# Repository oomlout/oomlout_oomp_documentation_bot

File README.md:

# None
## Description
None/

## Images

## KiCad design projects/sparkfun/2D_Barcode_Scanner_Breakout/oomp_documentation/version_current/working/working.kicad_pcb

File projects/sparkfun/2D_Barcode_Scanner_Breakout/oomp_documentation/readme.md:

# None

## Description
None/
## Schematic

## Bill of Materials
| Id | Designator | Footprint | Quantity | Designation | Supplier and ref |  |
| --- | --- | --- | --- | --- | --- | --- |
| 1 | R3,R2 | 0603 | 2 | 5.1k |  |  |
| 2 | U$1,U$7 | ##TRIG##0 | 2 |  |  |  |
| 3 | H2,H3 | STAND-OFF | 2 | STAND-OFF |  |  |
| 4 | J4 | 1X06_NO_SILK | 1 |  |  |  |
| 5 | J2 | USB-C-16P-2LAYER-PAD<br>S | 1 |  |  |  |
| 6 | S2 | TACTILE_SWITCH_SMD_5<br>.2MM | 1 | MOMENTARY-SWITCH-SPS<br>T-SMD-5.2MM-TALL |  |  |
| 7 | Q1,Q2 | SOT23-3 | 2 | 600mA/40V |  |  |
| 8 | U$8 | PWR0 | 1 |  |  |  |
| 9 | R1 | 0603 | 1 | 100 |  |  |
| 10 | U$17,U$18 | 2D_BARCODE0 | 2 |  |  |  |
| 11 | C2,C1 | 0603 | 2 | 1.0uF |  |  |
| 12 | D1 | LED-0603 | 1 | RED |  |  |
| 13 | FRAME1 | CREATIVE_COMMONS | 1 | FRAME-LETTER |  |  |
| 14 | U$26,U$27 | #TX_#0 | 2 |  |  |  |
| 15 | R7 | 0603 | 1 | 10 |  |  |
| 16 | U$32,U$33 | #GND_#0 | 2 |  |  |  |
| 17 | U$19 | SCANNER0 | 1 |  |  |  |
| 18 | U$30,U$31 | #RX_#0 | 2 |  |  |  |
| 19 | LS1 | BUZZER-CCV | 1 | BUZZER-SMD |  |  |
| 20 | U$3 | STAT0 | 1 |  |  |  |
| 21 | FD2,FD1,FD3,FD4 | FIDUCIAL-MICRO | 4 | FIDUCIALUFIDUCIAL |  |  |
| 22 | U1 | SOT23-5 | 1 | 3.3V |  |  |
| 23 | R9,R4,R11 | 0603 | 3 | 1k |  |  |
| 24 | U$28,U$29 | #3#3V_#0 | 2 |  |  |  |
| 25 | J3 | FPC_12_0.5MM | 1 |  |  |  |
| 26 | R8,R10 | 0603 | 2 | 10k |  |  |
| 27 | LOGO2 | SFE_LOGO_FLAME_.1 | 1 | SFE_LOGO_FLAME.1_INC<br>H |  |  |
| 28 | U$2,U$21 | #STAT_#0 | 2 |  |  |  |
| 29 | D2 | LED-0603 | 1 | GREEN |  |  |
| 30 | C3 | 0603 | 1 | 0.1uF |  |  |
| 31 | U$4 | #SCAN#0 | 1 |  |  |  |
| 32 | BUZZ0,PWR0,PWR_LED0 | SMT-JUMPER_2_NC_TRAC<br>E_SILK | 3 | JUMPER-SMT_2_NC_TRAC<br>E_SILK |  |  |
| 33 | U$9 | #LED#0 | 1 |  |  |  |
| 34 | U$6 | #STAT_LED#0 | 1 |  |  |  |
| 35 | LOGO1 | OSHW-LOGO-S | 1 | OSHW-LOGOS |  |  |
| 36 | U$20 | SCANNER_BREAKOUT0 | 1 |  |  |  |
| 37 | U2 | BARCODE_SCANNER_MOUN<br>T | 1 | BARCODE_SCANNER_MOUN<br>T |  |  |
| 38 | U$5 | #BUZZ#0 | 1 |  |  |  |
| 39 | LOGO3 | SFE_LOGO_NAME_.1 | 1 | SFE_LOGO_NAME.1_INCH |  |  |

## Images

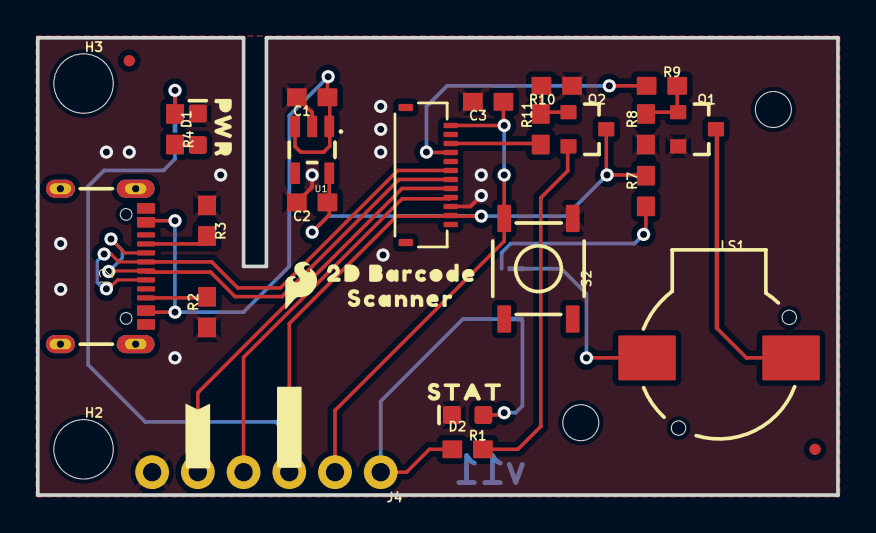
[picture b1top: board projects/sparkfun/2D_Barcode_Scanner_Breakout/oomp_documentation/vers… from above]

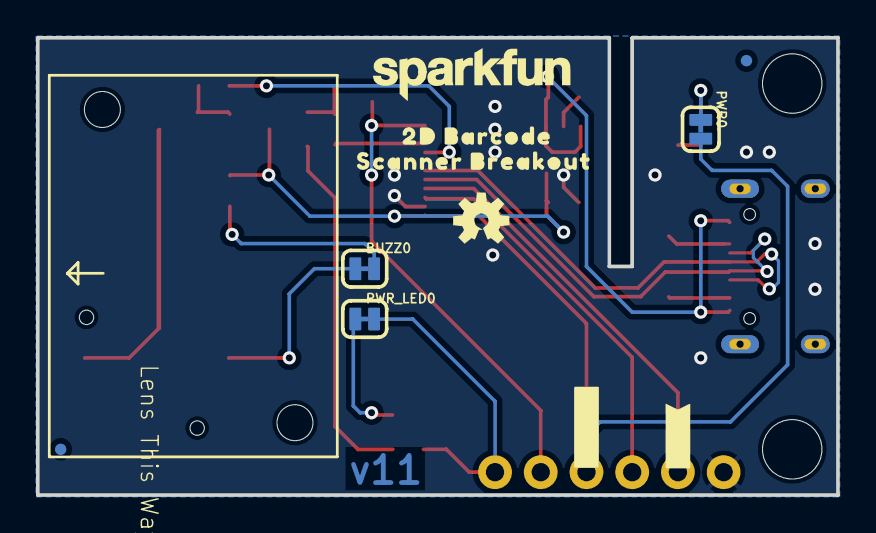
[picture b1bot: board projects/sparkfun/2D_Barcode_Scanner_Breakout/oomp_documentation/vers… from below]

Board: 2 copper layers, 44.5 x 25.4 mm, 58 parts (19 on the bottom side), 22 nets.

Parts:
BUZZ0: JUMPER-SMT_2_NC_TRACE_SILK; SMT-JUMPER_2_NC_TRACE_SILK
C1, C2: 1.0uF; 0603
C3: 0.1uF; 0603
D1: RED; LED-0603
D2: GREEN; LED-0603
FD1, FD2, FD3, FD4: FIDUCIALUFIDUCIAL; FIDUCIAL-MICRO
FRAME1: FRAME-LETTER; CREATIVE_COMMONS
H2, H3: STAND-OFF
J2: USB-C-16P-2LAYER-PADS
J3: FPC_12_0.5MM
J4: 1X06_NO_SILK
LOGO1: OSHW-LOGOS; OSHW-LOGO-S
LOGO2: SFE_LOGO_FLAME.1_INCH; SFE_LOGO_FLAME_.1
LOGO3: SFE_LOGO_NAME.1_INCH; SFE_LOGO_NAME_.1
LS1: BUZZER-SMD; BUZZER-CCV
PWR0: JUMPER-SMT_2_NC_TRACE_SILK; SMT-JUMPER_2_NC_TRACE_SILK
PWR_LED0: JUMPER-SMT_2_NC_TRACE_SILK; SMT-JUMPER_2_NC_TRACE_SILK
Q1, Q2: 600mA/40V; SOT23-3
R1: 100; 0603
R2, R3: 5.1k; 0603
R4, R9, R11: 1k; 0603
R7: 10; 0603
R8, R10: 10k; 0603
S2: MOMENTARY-SWITCH-SPST-SMD-5.2MM-TALL; TACTILE_SWITCH_SMD_5.2MM
U1: 3.3V; SOT23-5
U2: BARCODE_SCANNER_MOUNT
U$1, U$7: ##TRIG##0
U$2, U$21: #STAT_#0
U$3: STAT0
U$4: #SCAN#0
U$5: #BUZZ#0
U$6: #STAT_LED#0
U$8: PWR0
U$9: #LED#0
U$17, U$18: 2D_BARCODE0
U$19: SCANNER0
U$20: SCANNER_BREAKOUT0
U$26, U$27: #TX_#0
U$28, U$29: #3#3V_#0
U$30, U$31: #RX_#0
U$32, U$33: #GND_#0

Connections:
3.3V: C2.1, J3.11, J4.3, PWR0.2, Q2.3, R7.2, U1.5
5V: C1.1, J2.VBUS1, J2.VBUS2, U1.1, U1.3
BUZZER: J3.4, R9.1
CC3: J2.A5, R3.2
CC4: J2.B5, R2.2
GND: C1.2, C2.2, C3.2, D1.C, D2.C, J2.GND, J2.GND2, J3.10, J4.6, Q1.2, R2.1, R3.1, R8.1, R10.1, S2.1, U1.2
unnamed: BUZZ0.2, R7.1
unnamed: LS1.-, Q1.3
unnamed: BUZZ0.1, LS1.+
unnamed: Q2.2, R1.2
unnamed: Q1.1, R8.2, R9.2
unnamed: PWR0.1, R4.1
unnamed: Q2.1, R10.2, R11.2
unnamed: D2.A, PWR_LED0.1
unnamed: D1.A, R4.2
RXI: J3.9, J4.4
STATUS_LED: J3.3, R11.1
STATUS_OUT: J4.1, PWR_LED0.2, R1.1
TXO: J3.8, J4.5
USB_N: J2.A7, J2.B7, J3.7
USB_P: J2.A6, J2.B6, J3.6
~SCAN_TRIGGER: C3.1, J3.1, J4.2, S2.3

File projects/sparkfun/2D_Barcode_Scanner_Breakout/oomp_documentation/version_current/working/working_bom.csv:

"Id";"Designator";"Footprint";"Quantity";"Designation";"Supplier and ref";
1;"R3,R2";"0603";2;"5.1k";;;
2;"U$1,U$7";"##TRIG##0";2;"";;;
3;"H2,H3";"STAND-OFF";2;"STAND-OFF";;;
4;"J4";"1X06_NO_SILK";1;"";;;
5;"J2";"USB-C-16P-2LAYER-PADS";1;"";;;
6;"S2";"TACTILE_SWITCH_SMD_5.2MM";1;"MOMENTARY-SWITCH-SPST-SMD-5.2MM-TALL";;;
7;"Q1,Q2";"SOT23-3";2;"600mA/40V";;;
8;"U$8";"PWR0";1;"";;;
9;"R1";"0603";1;"100";;;
10;"U$17,U$18";"2D_BARCODE0";2;"";;;
11;"C2,C1";"0603";2;"1.0uF";;;
12;"D1";"LED-0603";1;"RED";;;
13;"FRAME1";"CREATIVE_COMMONS";1;"FRAME-LETTER";;;
14;"U$26,U$27";"#TX_#0";2;"";;;
15;"R7";"0603";1;"10";;;
16;"U$32,U$33";"#GND_#0";2;"";;;
17;"U$19";"SCANNER0";1;"";;;
18;"U$30,U$31";"#RX_#0";2;"";;;
19;"LS1";"BUZZER-CCV";1;"BUZZER-SMD";;;
20;"U$3";"STAT0";1;"";;;
21;"FD2,FD1,FD3,FD4";"FIDUCIAL-MICRO";4;"FIDUCIALUFIDUCIAL";;;
22;"U1";"SOT23-5";1;"3.3V";;;
23;"R9,R4,R11";"0603";3;"1k";;;
24;"U$28,U$29";"#3#3V_#0";2;"";;;
25;"J3";"FPC_12_0.5MM";1;"";;;
26;"R8,R10";"0603";2;"10k";;;
27;"LOGO2";"SFE_LOGO_FLAME_.1";1;"SFE_LOGO_FLAME.1_INCH";;;
28;"U$2,U$21";"#STAT_#0";2;"";;;
29;"D2";"LED-0603";1;"GREEN";;;
30;"C3";"0603";1;"0.1uF";;;
31;"U$4";"#SCAN#0";1;"";;;
32;"BUZZ0,PWR0,PWR_LED0";"SMT-JUMPER_2_NC_TRACE_SILK";3;"JUMPER-SMT_2_NC_TRACE_SILK";;;
33;"U$9";"#LED#0";1;"";;;
34;"U$6";"#STAT_LED#0";1;"";;;
35;"LOGO1";"OSHW-LOGO-S";1;"OSHW-LOGOS";;;
36;"U$20";"SCANNER_BREAKOUT0";1;"";;;
37;"U2";"BARCODE_SCANNER_MOUNT";1;"BARCODE_SCANNER_MOUNT";;;
38;"U$5";"#BUZZ#0";1;"";;;
39;"LOGO3";"SFE_LOGO_NAME_.1";1;"SFE_LOGO_NAME.1_INCH";;;

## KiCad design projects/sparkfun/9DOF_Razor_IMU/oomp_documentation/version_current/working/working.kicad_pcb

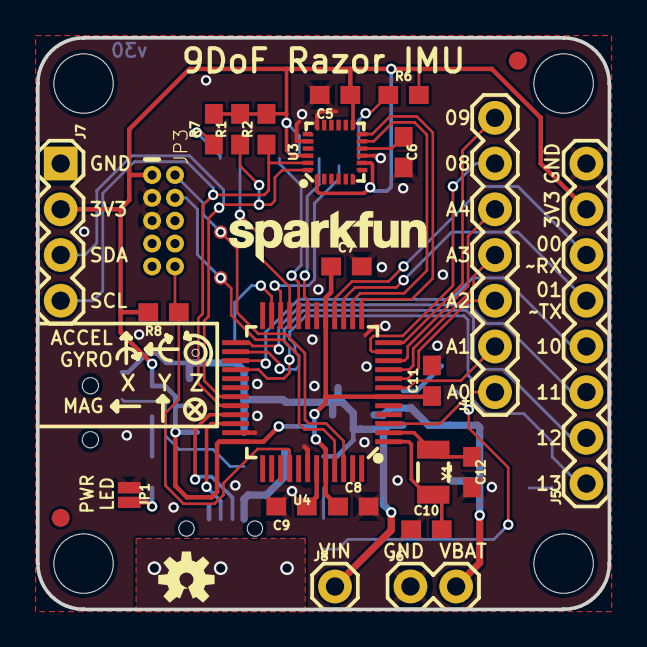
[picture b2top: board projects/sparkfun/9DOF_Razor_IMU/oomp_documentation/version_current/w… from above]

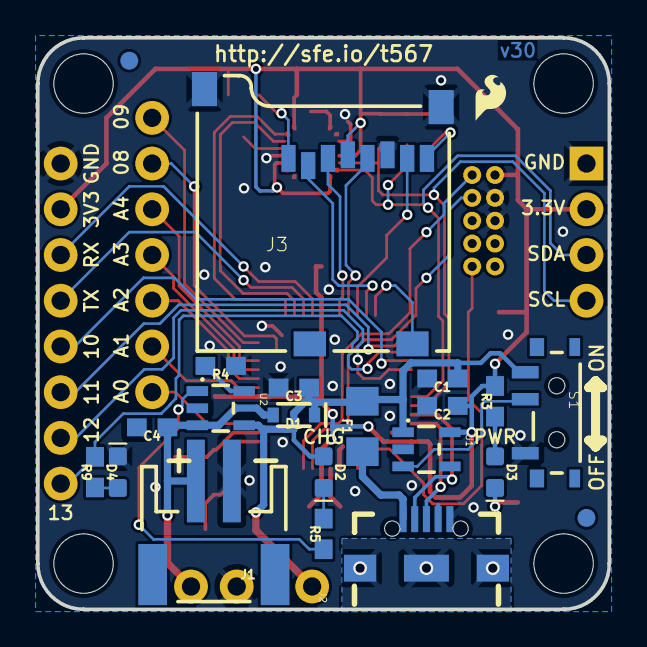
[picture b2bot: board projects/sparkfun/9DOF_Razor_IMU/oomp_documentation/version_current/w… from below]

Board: 2 copper layers, 31.8 x 31.8 mm, 56 parts (22 on the bottom side), 46 nets.

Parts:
C1: 1.0uF; 0603
C2: 2.2uF; 0603
C3, C4: 4.7uF; 0603
C5, C6, C7, C8, C9, C11: 0.1uF; 0603
C10, C12: 15pF; 0603
D1: 1A/23V/620mV; SOD-323
D2: Yellow; LED-0603
D3: RED; LED-0603
D4: BLUE; LED-0603
F1: 6V/0.5A; 1206
FD1, FD2, FD3, FD4: FIDUCIAL1X2; FIDUCIAL-1X2
FRAME1: FRAME-LETTER; CREATIVE_COMMONS
H1, H2, H3, H4: STAND-OFF
J1: LiPo; JST-2-SMD
J2: USB-B-MICRO-SMD_V03
J3: USD_CONNECTOR; MICRO-SD-SOCKET-PP
J4: 1X07
J5: 1X08
J6: 1X02
J7: 1X04
J8: 1X01
JP1: LED; SMT-JUMPER_2_NC_PASTE_NO-SILK
JP3: CORTEX_DEBUGPTH; 2X5-PTH-1.27MM
LOGO1: SFE_LOGO_FLAME.1_INCH; SFE_LOGO_FLAME_.1
LOGO2: OSHW-LOGOS; OSHW-LOGO-S
LOGO3: SFE_LOGO_NAME.1_INCH; SFE_LOGO_NAME_.1
R1, R2: 4.7k; 0603
R3, R5, R9: 1k; 0603
R4: 2.2k; 0603
R6, R7: 100k; 0603
R8: 10k; 0603
S1: SWITCH-SPST-SMD-A
TP1, TP2: TEST-POINT3; PAD.03X.03
U1: 3.3V; SOT23-5
U2: MCP73831; SOT23-5
U3: MPU-9250; QFN24-3X3
U4: ATSAMD21G-A; TQFP-48
Y1: 32.768kHz; CRYSTAL-SMD-3.2X1.5MM

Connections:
3.3V: C2.1, C5.1, C7.1, C8.1, C11.1, J3.VCC, J5.7, J7.2, JP3.1, R1.2, R2.2, R3.2, R6.2, R7.2, R8.2, U1.5, U3.1, U3.8, U3.13, U3.22, U4.6, U4.17, U4.36, U4.44
A0: J4.1, U4.3
A1: J4.2, U4.7
A2: J4.3, U4.8
A3: J4.4, U4.9
A4: J4.5, U4.10
CHG_LED: R5.1, U2.1
D0/RXI: J5.6, U4.16
D1/TXO: J5.5, U4.15
D2/SD_CD: J3.CD1, U4.23
D3/FSYNC: U3.11, U4.14
D4/INT: U3.12, U4.13
D8: J4.6, U4.11
D9: J4.7, U4.12
D10: J5.4, U4.27
D11: J5.3, U4.25
D12: J5.2, U4.28
D13: J5.1, R9.2, U4.26
D+: J2.D+, U4.34
D-: J2.D-, U4.33
GND: C1.2, C2.2, C3.2, C4.2, C5.2, C6.2, C7.2, C8.2, C9.2, C10.1, C11.2, C12.2, D4.C, J1.1, J2.GND, J3.GND, J3.GND1, J3.GND3, J5.8, J6.1, J7.1, JP1.1, JP3.3, JP3.5, R4.1, S1.3, U1.2, U2.2, U3.9, U3.18, U3.20, U4.5, U4.18, U4.35, U4.42
unnamed: F1.1, J2.VBUS
unnamed: C10.2, U4.1, Y1.P$2
unnamed: D4.A, R9.1
unnamed: C12.1, U4.2, Y1.P$1
unnamed: D3.A, R3.1
unnamed: R4.2, U2.5
unnamed: J3.RSV1, R6.1
unnamed: J3.RSV2, R7.1
unnamed: D2.C, R5.2
unnamed: D3.C, JP1.2
REGOUT: C6.1, U3.10
SCL: J7.4, R2.1, U3.23, U4.32
SDA: J7.3, R1.1, U3.24, U4.31
SD_MISO: J3.DO, U4.21
SD_MOSI: J3.DI, U4.19
SD_SCK: J3.SCLK, U4.20
SD_~CS: J3.CS, U4.22
SHIELD: J2.SHIELD1, J2.SHIELD2, J2.SHIELD3
SWCLK: JP3.4, TP1.P$1, U4.45
SWDIO: JP3.2, TP2.P$1, U4.46
VDDCORE: C9.1, U4.43
VIN: C1.1, C3.1, D1.C, D2.A, F1.2, J8.1, S1.1, U1.1, U2.4
VREG_EN: S1.2, U1.3
V_BATT: C4.1, D1.A, J1.2, J6.2, U2.3
~RESET: JP3.10, R8.1, U4.40

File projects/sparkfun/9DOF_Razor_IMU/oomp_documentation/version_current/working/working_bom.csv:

"Id";"Designator";"Footprint";"Quantity";"Designation";"Supplier and ref";
1;"H1,H2,H3,H4";"STAND-OFF";4;"STAND-OFF";;;
2;"C11,C5,C7,C9,C8,C6";"0603";6;"0.1uF";;;
3;"U4";"TQFP-48";1;"ATSAMD21G-A";;;
4;"C12,C10";"0603";2;"15pF";;;
5;"FD2,FD4,FD3,FD1";"FIDUCIAL-1X2";4;"FIDUCIAL1X2";;;
6;"Y1";"CRYSTAL-SMD-3.2X1.5MM";1;"32.768kHz";;;
7;"R6,R7";"0603";2;"100k";;;
8;"R1,R2";"0603";2;"4.7k";;;
9;"JP1";"SMT-JUMPER_2_NC_PASTE_NO-SILK";1;"LED";;;
10;"LOGO2";"OSHW-LOGO-S";1;"OSHW-LOGOS";;;
11;"J6";"1X02";1;"";;;
12;"LOGO3";"SFE_LOGO_NAME_.1";1;"SFE_LOGO_NAME.1_INCH";;;
13;"TP2,TP1";"PAD.03X.03";2;"TEST-POINT3";;;
14;"J4";"1X07";1;"";;;
15;"FRAME1";"CREATIVE_COMMONS";1;"FRAME-LETTER";;;
16;"R8";"0603";1;"10k";;;
17;"U3";"QFN24-3X3";1;"MPU-9250";;;
18;"JP3";"2X5-PTH-1.27MM";1;"CORTEX_DEBUGPTH";;;
19;"J8";"1X01";1;"";;;
20;"J7";"1X04";1;"";;;
21;"J5";"1X08";1;"";;;
22;"D3";"LED-0603";1;"RED";;;
23;"S1";"SWITCH-SPST-SMD-A";1;"SWITCH-SPST-SMD-A";;;
24;"D1";"SOD-323";1;"1A/23V/620mV";;;
25;"C2";"0603";1;"2.2uF";;;
26;"C3,C4";"0603";2;"4.7uF";;;
27;"R3,R5,R9";"0603";3;"1k";;;
28;"J3";"MICRO-SD-SOCKET-PP";1;"USD_CONNECTOR";;;
29;"F1";"1206";1;"6V/0.5A";;;
30;"C1";"0603";1;"1.0uF";;;
31;"LOGO1";"SFE_LOGO_FLAME_.1";1;"SFE_LOGO_FLAME.1_INCH";;;
32;"U1";"SOT23-5";1;"3.3V";;;
33;"J2";"USB-B-MICRO-SMD_V03";1;"";;;
34;"J1";"JST-2-SMD";1;"LiPo";;;
35;"R4";"0603";1;"2.2k";;;
36;"U2";"SOT23-5";1;"MCP73831";;;
37;"D2";"LED-0603";1;"Yellow";;;
38;"D4";"LED-0603";1;"BLUE";;;

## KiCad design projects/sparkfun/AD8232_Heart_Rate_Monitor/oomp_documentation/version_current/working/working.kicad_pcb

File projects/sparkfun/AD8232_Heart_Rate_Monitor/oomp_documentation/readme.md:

# None

## Description
None/
## Schematic

## Bill of Materials
| Id | Designator | Footprint | Quantity | Designation | Supplier and ref |  |
| --- | --- | --- | --- | --- | --- | --- |
| 1 | JP3 | 1X06 | 1 |  |  |  |
| 2 | C1 | 0603-CAP | 1 | 1.5nF |  |  |
| 3 | STANDOFF1,STANDOFF4,<br>STANDOFF3,STANDOFF2 | STAND-OFF | 4 | STAND-OFF |  |  |
| 4 | LOGO2 | SFE_LOGO_NAME_FLAME_<br>.1 | 1 | SFE_LOGO_NAME_FLAME.<br>1_INCH |  |  |
| 5 | U1 | LFCSP_20 | 1 | AD8232 |  |  |
| 6 | FRAME1 | CREATIVE_COMMONS | 1 | FRAME-LETTER |  |  |
| 7 | C7 | 0603-CAP | 1 | 0.1uf |  |  |
| 8 | R2,R13,R1,R14,R11,R1<br>0 | 0603-RES | 6 | 10M |  |  |
| 9 | R6,R7,R9 | 0603-RES | 3 | 1M |  |  |
| 10 | FID1,FID2 | FIDUCIAL-1X2 | 2 | FIDUCIAL1X2 |  |  |
| 11 | R3,R4 | 0603-RES | 2 | 180k |  |  |
| 12 | SJ4 | SJ_2S-TRACE | 1 | LED DISABLE |  |  |
| 13 | R15 | 0603-RES | 1 | 10K |  |  |
| 14 | R5 | 0603-RES | 1 | 360k |  |  |
| 15 | R18,R20 | 0603 | 2 | DNP |  |  |
| 16 | R8 | 0603-RES | 1 | 100k |  |  |
| 17 | C4,C6 | 0805 | 2 | 0.33uF |  |  |
| 18 | D1 | LED-0603 | 1 | RED |  |  |
| 19 | R16 | 0603-RES | 1 | 1k |  |  |
| 20 | C3 | 0603-CAP | 1 | 10nF |  |  |
| 21 | LOGO1 | OSHW-LOGO-S | 1 | OSHW-LOGOS |  |  |
| 22 | C5 | 0603-CAP | 1 | 0.1uF |  |  |
| 23 | JP2 | AUDIO-JACK-3.5MM-SMD | 1 |  |  |  |
| 24 | R12 | 0603-RES | 1 | 1.4M |  |  |
| 25 | R17,R19 | 0603 | 2 | 0 |  |  |
| 26 | C2 | 0603-CAP | 1 | 1nF |  |  |
| 27 | JP1 | 1X03 | 1 |  |  |  |

## Images

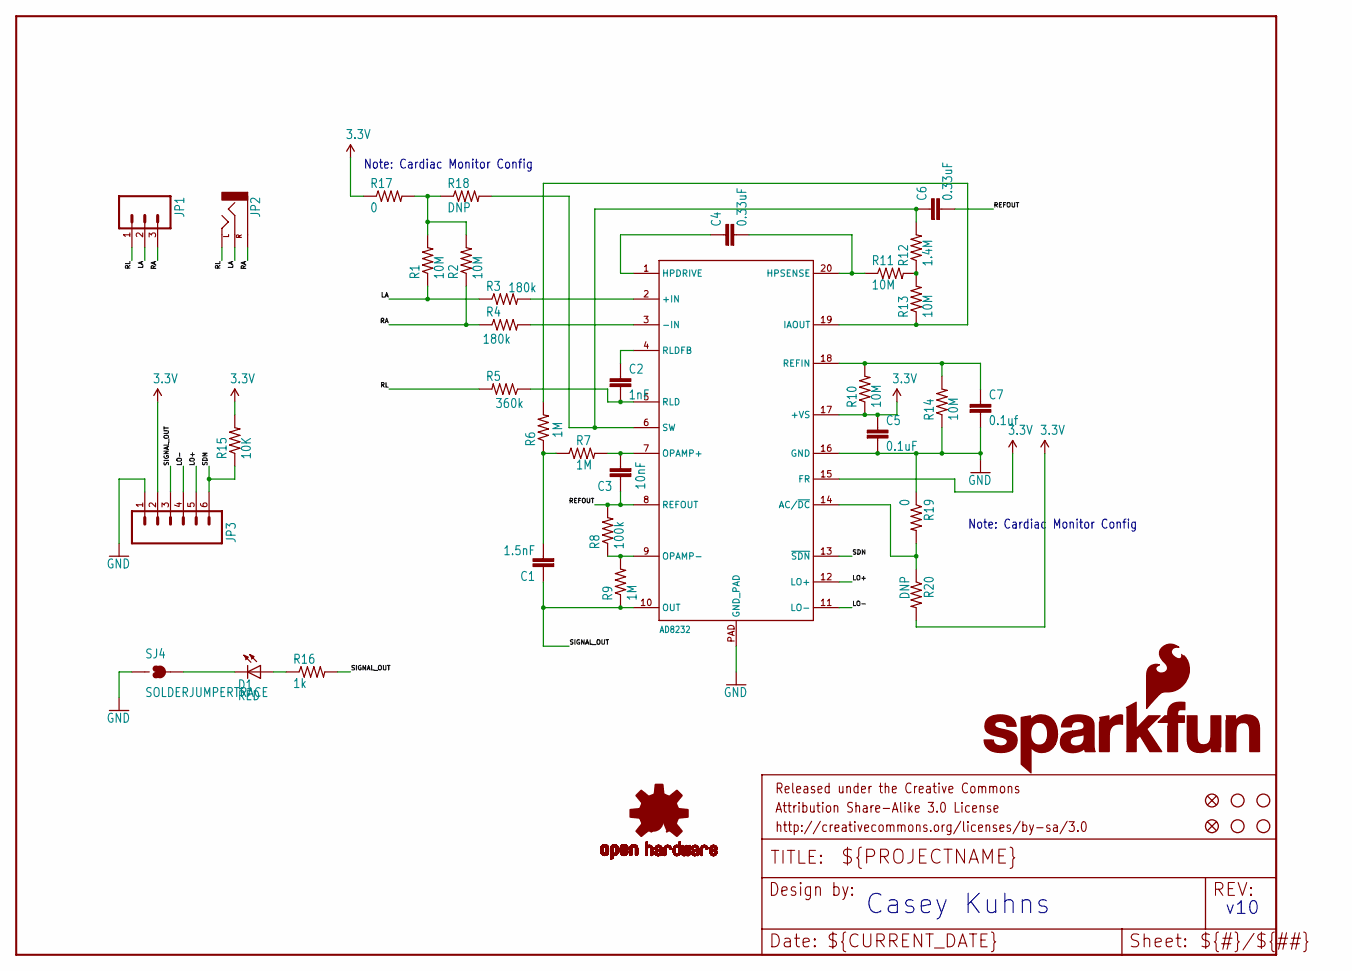
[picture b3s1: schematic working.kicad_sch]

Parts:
C1: 1.5nF; 0603-CAP
C2: 1nF; 0603-CAP
C3: 10nF; 0603-CAP
C4, C6: 0.33uF; 0805
C5: 0.1uF; 0603-CAP
C7: 0.1uf; 0603-CAP
D1: RED; LED-0603
FID1, FID2: FIDUCIAL1X2; FIDUCIAL-1X2
FRAME1: FRAME-LETTER; CREATIVE_COMMONS
JP1: M03PTH; 1X03
JP2: AUDIO-JACKSMD2; AUDIO-JACK-3.5MM-SMD
JP3: M06SIP; 1X06
LOGO1: OSHW-LOGOS; OSHW-LOGO-S
LOGO2: SFE_LOGO_NAME_FLAME.1_INCH; SFE_LOGO_NAME_FLAME_.1
R1, R2, R10, R11, R13, R14: 10M; 0603-RES
R3, R4: 180k; 0603-RES
R5: 360k; 0603-RES
R6, R7, R9: 1M; 0603-RES
R8: 100k; 0603-RES
R12: 1.4M; 0603-RES
R15: 10K; 0603-RES
R16: 1k; 0603-RES
R17, R19: 0; 0603
R18, R20: DNP; 0603
SJ4: SOLDERJUMPERTRACE; SJ_2S-TRACE
STANDOFF1, STANDOFF2, STANDOFF3, STANDOFF4: STAND-OFF
U1: AD8232; LFCSP_20

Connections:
3.3V: C5.1, JP3.2, R10.1, R15.2, R17.1, R20.2, U1.15 (FR), U1.17 (+VS)
GND: C5.2, C7.2, JP3.1, R14.1, R19.1, SJ4.1, U1.16 (GND), U1.PAD (GND_PAD)
LA: JP1.2, JP2.RING (RIGHT), R1.1, R3.1
LO+: JP3.5, U1.12 (LO+)
LO-: JP3.4, U1.11 (LO-)
unnamed: R3.2, U1.2 (+IN)
unnamed: R4.2, U1.3 (-IN)
unnamed: C3.2, R7.2, U1.7 (OPAMP+)
unnamed: C4.2, R11.1, U1.20 (HPSENSE)
unnamed: C7.1, R10.2, R14.2, U1.18 (REFIN)
unnamed: D1.A, R16.1
unnamed: R8.1, R9.2, U1.9 (OPAMP-)
unnamed: R6.2, R13.1, U1.19 (IAOUT)
unnamed: C1.2, R6.1, R7.1
unnamed: D1.C, SJ4.2
unnamed: R19.2, R20.1, U1.14 (AC/~DC)
unnamed: C4.1, U1.1 (HPDRIVE)
unnamed: R11.2, R12.1, R13.2
unnamed: C6.1, R12.2, R18.2, U1.6 (SW)
unnamed: C2.1, U1.4 (RLDFB)
unnamed: C2.2, R5.1, U1.5 (RLD)
unnamed: R1.2, R2.2, R17.2, R18.1
RA: JP1.3, JP2.SLEEVE, R2.1, R4.1
REFOUT: C3.1, C6.2, R8.2, U1.8 (REFOUT)
RL: JP1.1, JP2.TIP (LEFT), R5.2
SDN: JP3.6, R15.1, U1.13 (~SDN)
SIGNAL_OUT: C1.1, JP3.3, R9.1, R16.2, U1.10 (OUT)

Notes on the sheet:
v10
Casey Kuhns
Note: Cardiac Monitor Config

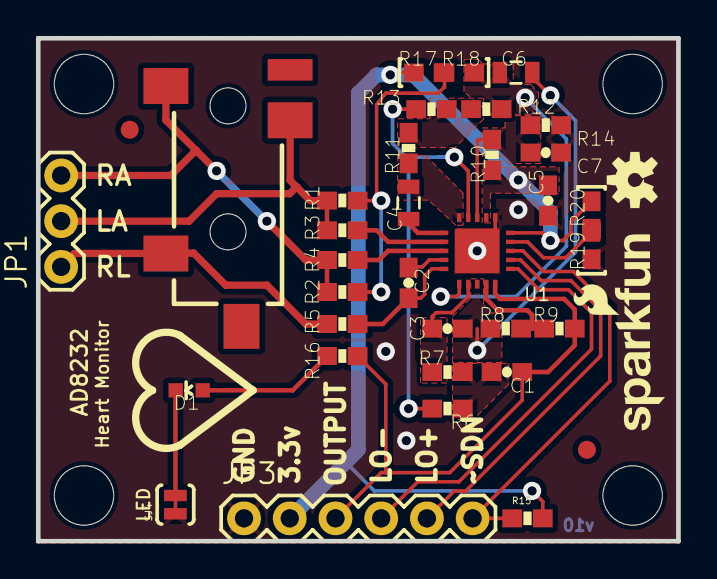
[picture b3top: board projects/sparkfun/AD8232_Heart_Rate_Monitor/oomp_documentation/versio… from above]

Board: 2 copper layers, 35.6 x 27.9 mm, 42 parts (0 on the bottom side), 27 nets.

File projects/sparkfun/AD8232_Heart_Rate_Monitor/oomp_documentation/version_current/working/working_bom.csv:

"Id";"Designator";"Footprint";"Quantity";"Designation";"Supplier and ref";
1;"JP3";"1X06";1;"";;;
2;"C1";"0603-CAP";1;"1.5nF";;;
3;"STANDOFF1,STANDOFF4,STANDOFF3,STANDOFF2";"STAND-OFF";4;"STAND-OFF";;;
4;"LOGO2";"SFE_LOGO_NAME_FLAME_.1";1;"SFE_LOGO_NAME_FLAME.1_INCH";;;
5;"U1";"LFCSP_20";1;"AD8232";;;
6;"FRAME1";"CREATIVE_COMMONS";1;"FRAME-LETTER";;;
7;"C7";"0603-CAP";1;"0.1uf";;;
8;"R2,R13,R1,R14,R11,R10";"0603-RES";6;"10M";;;
9;"R6,R7,R9";"0603-RES";3;"1M";;;
10;"FID1,FID2";"FIDUCIAL-1X2";2;"FIDUCIAL1X2";;;
11;"R3,R4";"0603-RES";2;"180k";;;
12;"SJ4";"SJ_2S-TRACE";1;"LED DISABLE";;;
13;"R15";"0603-RES";1;"10K";;;
14;"R5";"0603-RES";1;"360k";;;
15;"R18,R20";"0603";2;"DNP";;;
16;"R8";"0603-RES";1;"100k";;;
17;"C4,C6";"0805";2;"0.33uF";;;
18;"D1";"LED-0603";1;"RED";;;
19;"R16";"0603-RES";1;"1k";;;
20;"C3";"0603-CAP";1;"10nF";;;
21;"LOGO1";"OSHW-LOGO-S";1;"OSHW-LOGOS";;;
22;"C5";"0603-CAP";1;"0.1uF";;;
23;"JP2";"AUDIO-JACK-3.5MM-SMD";1;"";;;
24;"R12";"0603-RES";1;"1.4M";;;
25;"R17,R19";"0603";2;"0";;;
26;"C2";"0603-CAP";1;"1nF";;;
27;"JP1";"1X03";1;"";;;

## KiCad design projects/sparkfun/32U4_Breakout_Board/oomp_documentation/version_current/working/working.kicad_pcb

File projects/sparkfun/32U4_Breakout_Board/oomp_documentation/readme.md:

# None

## Description
None/
## Schematic

## Bill of Materials
| Id | Designator | Footprint | Quantity | Designation | Supplier and ref |  |
| --- | --- | --- | --- | --- | --- | --- |
| 1 | JP7,JP6 | FIDUCIAL-1X2 | 2 | FIDUCIAL1X2 |  |  |
| 2 | J1 | 2X3 | 1 | AVR_SPI_PRG |  |  |
| 3 | C6,C9,C1,C7 | 0603-CAP | 4 | 0.1uF |  |  |
| 4 | JP5 | SFE-LOGO-FLAME | 1 | LOGO-SFESK |  |  |
| 5 | C8 | EIA3216 | 1 | 10uF |  |  |
| 6 | R2,R3 | 0603-RES | 2 | 22 |  |  |
| 7 | C4,C5 | 0603-CAP | 2 | 1uF |  |  |
| 8 | X1 | USB-MINIB | 1 | USBSMD |  |  |
| 9 | R1 | 0603-RES | 1 | 10k |  |  |
| 10 | R4 | 0603-RES | 1 | 1k |  |  |
| 11 | C2,C3 | 0603-CAP | 2 | 18pF |  |  |
| 12 | U2 | SOT23-5 | 1 | 3.3V_REG_LDOSMD |  |  |
| 13 | U1 | QFN-44-NOPAD_1_1 | 1 | ATMEGA32U4 |  |  |
| 14 | LED1 | LED-0603 | 1 | Power |  |  |
| 15 | S1 | TACTILE_SWITCH_SMD | 1 | SWITCH-SMD |  |  |
| 16 | Y1 | CRYSTAL-SMD-5X3 | 1 | 16MHz |  |  |
| 17 | SJ1 | SJ_3_PASTE2&3 | 1 | Power Select |  |  |
| 18 | F1 | PTC-1206 | 1 | PTCSMD |  |  |
| 19 | JP8 | SFE-NEW-WEBLOGO | 1 | LOGO-SFENEW |  |  |
| 20 | JP3 | 1X06 | 1 |  |  |  |
| 21 | JP1,JP2 | 1X12 | 2 | M12PTH |  |  |
| 22 | U$6 | OSHW-LOGO-M | 1 | OSHW-LOGOM |  |  |

## Images

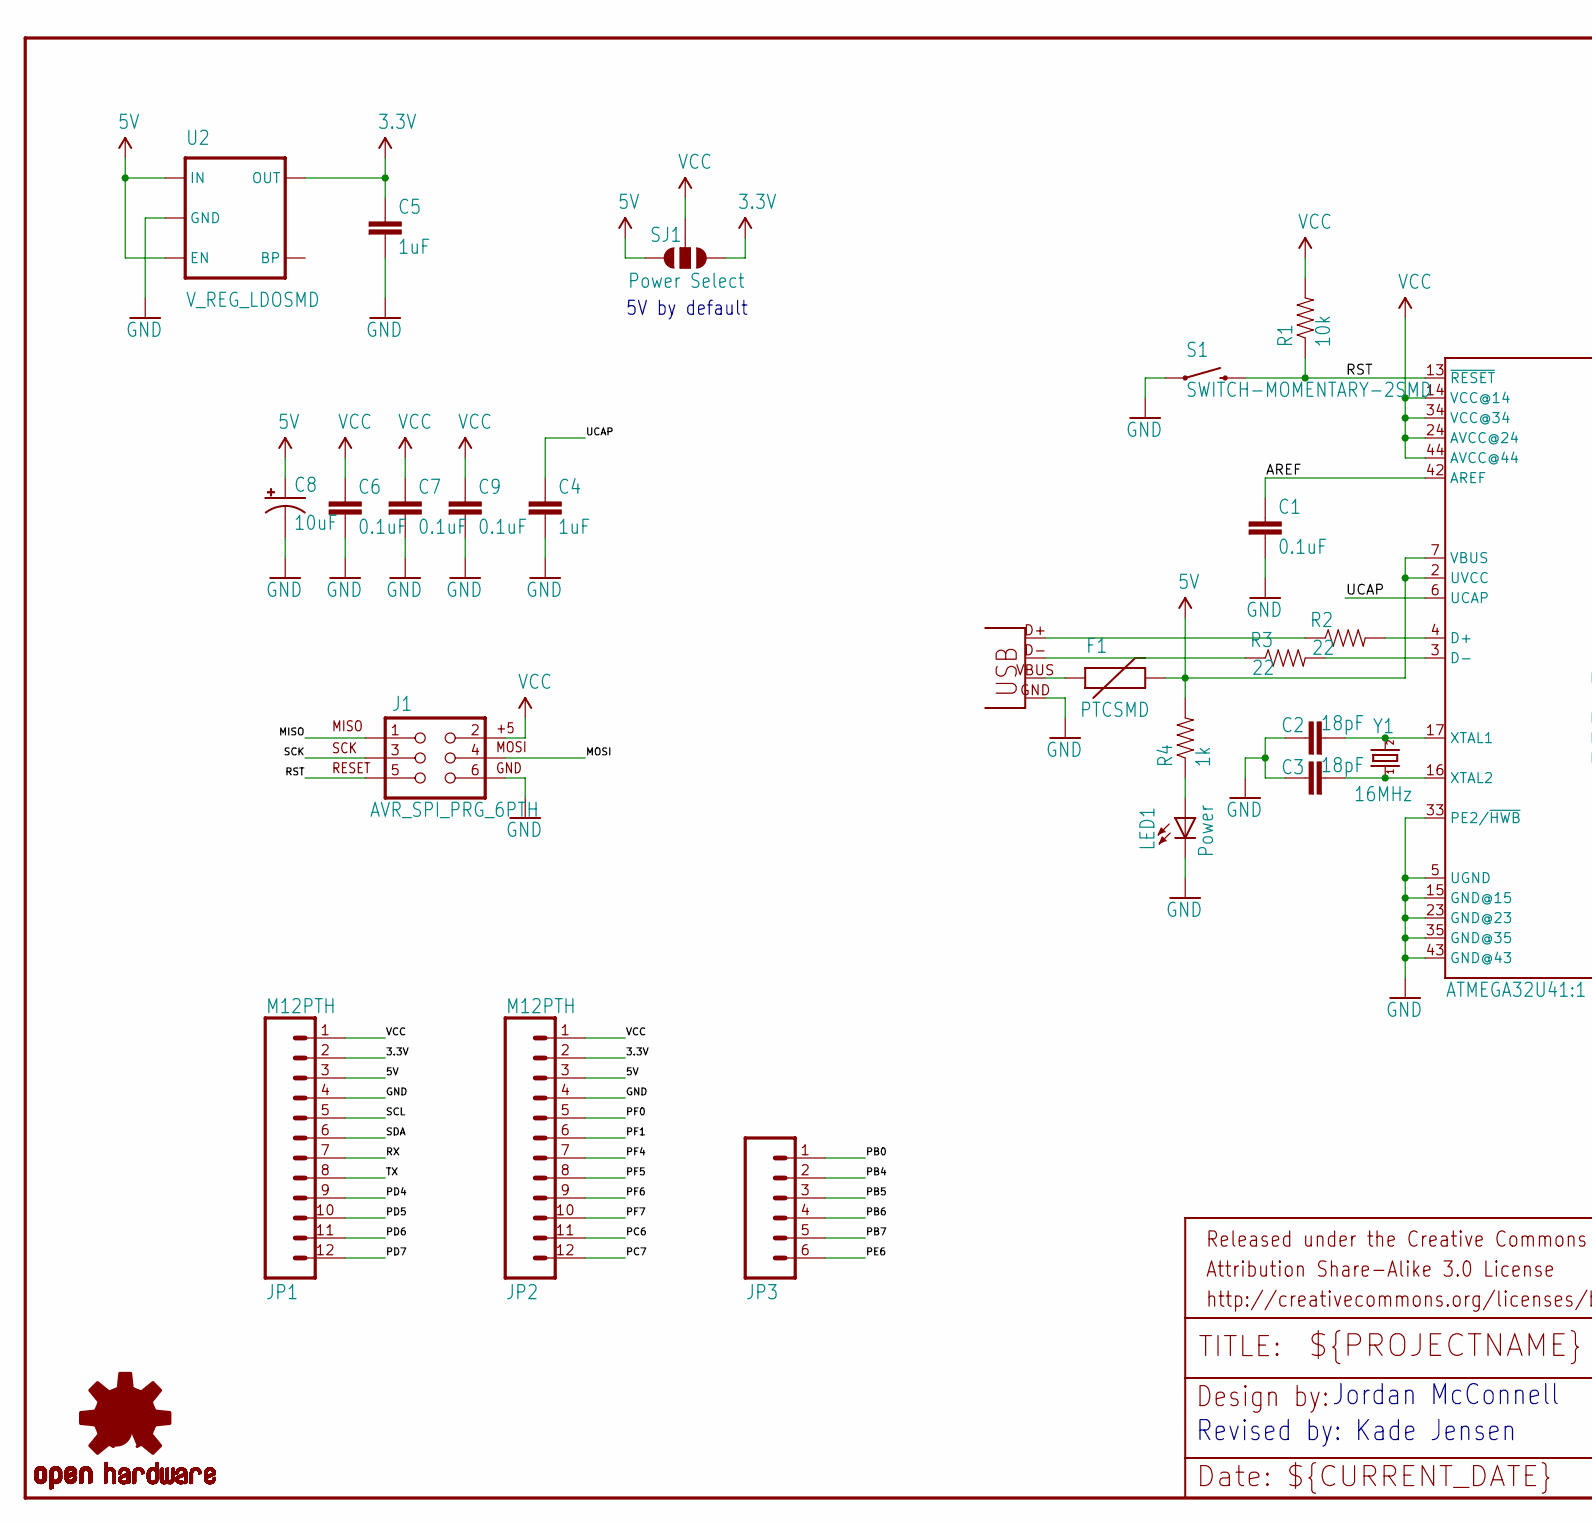
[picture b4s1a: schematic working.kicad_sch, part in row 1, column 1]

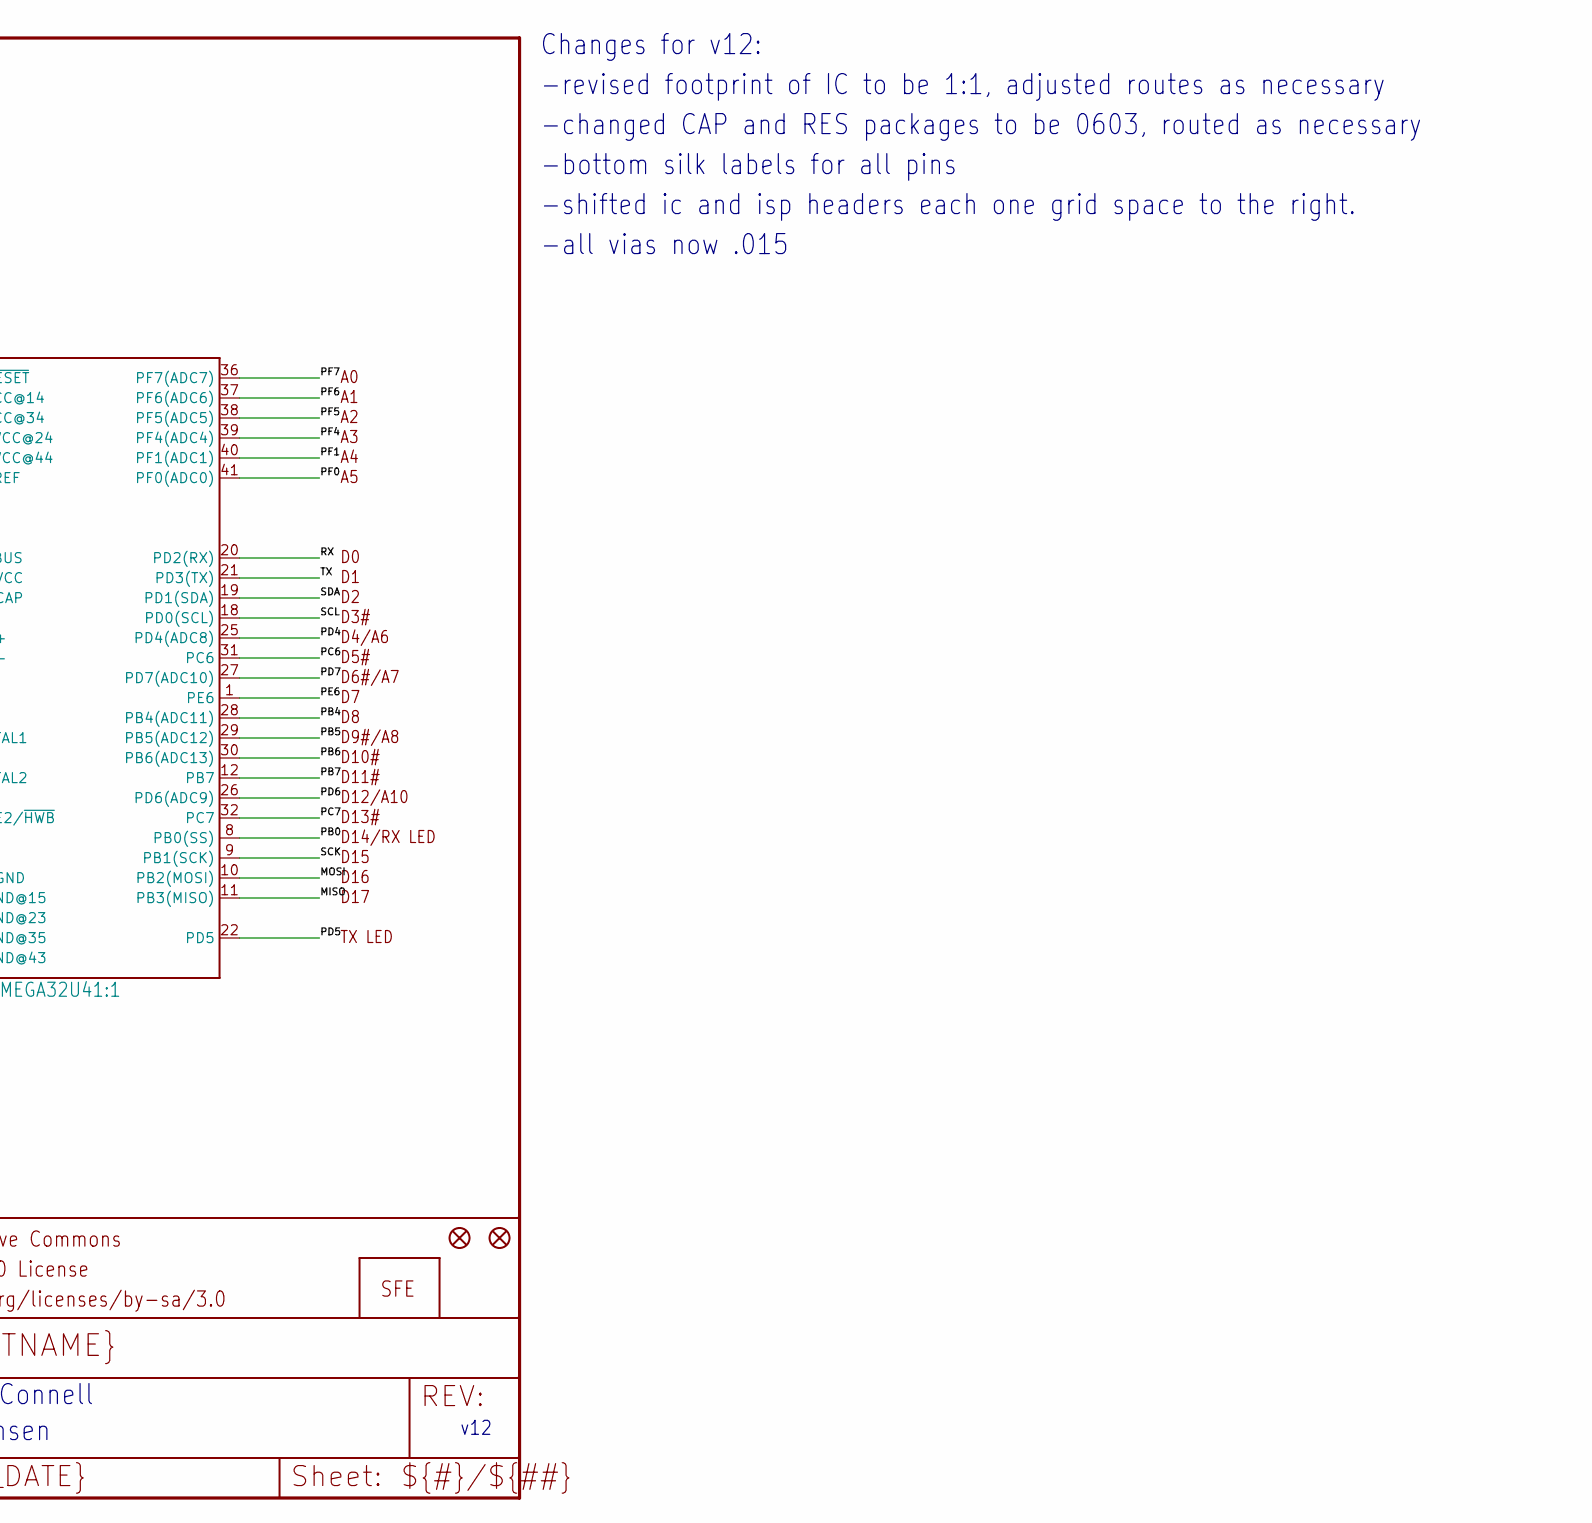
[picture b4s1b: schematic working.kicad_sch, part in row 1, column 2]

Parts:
C1, C6, C7, C9: 0.1uF; 0603-CAP
C2, C3: 18pF; 0603-CAP
C4, C5: 1uF; 0603-CAP
C8: 10uF; EIA3216
F1: PTCSMD; PTC-1206
J1: AVR_SPI_PRG_6PTH; 2X3
JP1, JP2: M12PTH; 1X12
JP3: M06SIP; 1X06
JP6, JP7: FIDUCIAL1X2; FIDUCIAL-1X2
JP8: LOGO-SFENEW; SFE-NEW-WEBLOGO
LED1: Power; LED-0603
R1: 10k; 0603-RES
R2, R3: 22; 0603-RES
R4: 1k; 0603-RES
S1: SWITCH-MOMENTARY-2SMD; TACTILE_SWITCH_SMD
SJ1: Power Select; SJ_3_PASTE2&3
U1: ATMEGA32U41:1; QFN-44-NOPAD_1_1
U2: V_REG_LDOSMD; SOT23-5
U$6: OSHW-LOGOM; OSHW-LOGO-M
X1: USBSMD; USB-MINIB
Y1: 16MHz; CRYSTAL-SMD-5X3

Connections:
3.3V: C5.1, JP1.2, JP2.2, SJ1.1, U2.5 (OUT)
5V: C8.A (+), F1.2, JP1.3, JP2.3, R4.2, SJ1.3, U1.2 (UVCC), U1.7 (VBUS), U2.1 (IN), U2.3 (EN)
AREF: C1.1, U1.42 (AREF)
D+: R2.1, X1.D+
D-: R3.1, X1.D-
GND: C1.2, C2.1, C3.1, C4.2, C5.2, C6.2, C7.2, C8.C (-), C9.2, J1.6, JP1.4, JP2.4, LED1.C, S1.1, U1.5 (UGND), U1.15 (GND@15), U1.23 (GND@23), U1.33 (PE2/~HWB), U1.35 (GND@35), U1.43 (GND@43), U2.2 (GND), X1.GND
MISO: J1.1, U1.11 (PB3(MISO))
MOSI: J1.4, U1.10 (PB2(MOSI))
unnamed: C2.2, U1.17 (XTAL1), Y1.3 (2)
unnamed: C3.2, U1.16 (XTAL2), Y1.1
unnamed: F1.1, X1.VBUS
unnamed: R2.2, U1.4 (D+)
unnamed: R3.2, U1.3 (D-)
unnamed: LED1.A, R4.1
PB0: JP3.1, U1.8 (PB0(SS))
PB4: JP3.2, U1.28 (PB4(ADC11))
PB5: JP3.3, U1.29 (PB5(ADC12))
PB6: JP3.4, U1.30 (PB6(ADC13))
PB7: JP3.5, U1.12 (PB7)
PC6: JP2.11, U1.31 (PC6)
PC7: JP2.12, U1.32 (PC7)
PD4: JP1.9, U1.25 (PD4(ADC8))
PD5: JP1.10, U1.22 (PD5)
PD6: JP1.11, U1.26 (PD6(ADC9))
PD7: JP1.12, U1.27 (PD7(ADC10))
PE6: JP3.6, U1.1 (PE6)
PF0: JP2.5, U1.41 (PF0(ADC0))
PF1: JP2.6, U1.40 (PF1(ADC1))
PF4: JP2.7, U1.39 (PF4(ADC4))
PF5: JP2.8, U1.38 (PF5(ADC5))
PF6: JP2.9, U1.37 (PF6(ADC6))
PF7: JP2.10, U1.36 (PF7(ADC7))
RST: J1.5, R1.1, S1.3 (2), U1.13 (~RESET)
RX: JP1.7, U1.20 (PD2(RX))
SCK: J1.3, U1.9 (PB1(SCK))
SCL: JP1.5, U1.18 (PD0(SCL))
SDA: JP1.6, U1.19 (PD1(SDA))
TX: JP1.8, U1.21 (PD3(TX))
UCAP: C4.1, U1.6 (UCAP)
VCC: C6.1, C7.1, C9.1, J1.2, JP1.1, JP2.1, R1.2, SJ1.2, U1.14 (VCC@14), U1.24 (AVCC@24), U1.34 (VCC@34), U1.44 (AVCC@44)

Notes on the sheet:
Changes for v12:
5V by default
Revised by: Kade Jensen
Jordan McConnell
v12
-shifted ic and isp headers each one grid space to the right.
-revised footprint of IC to be 1:1, adjusted routes as necessary
-bottom silk labels for all pins
-changed CAP and RES packages to be 0603, routed as necessary
-all vias now .015

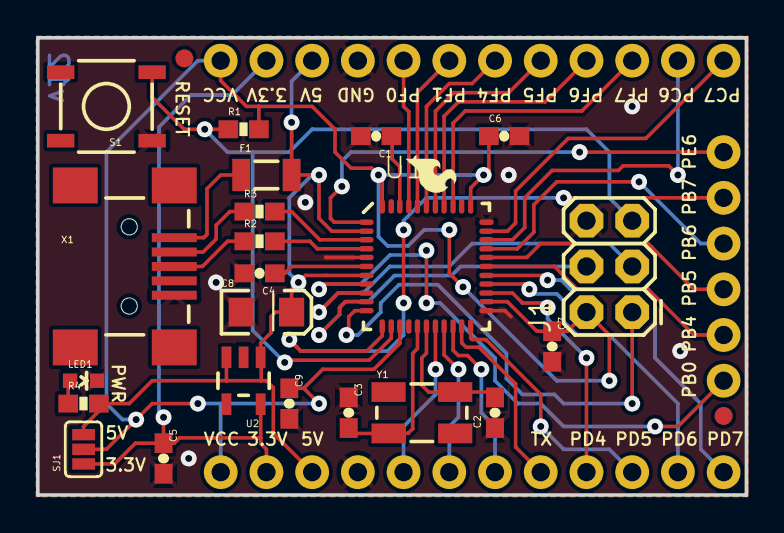
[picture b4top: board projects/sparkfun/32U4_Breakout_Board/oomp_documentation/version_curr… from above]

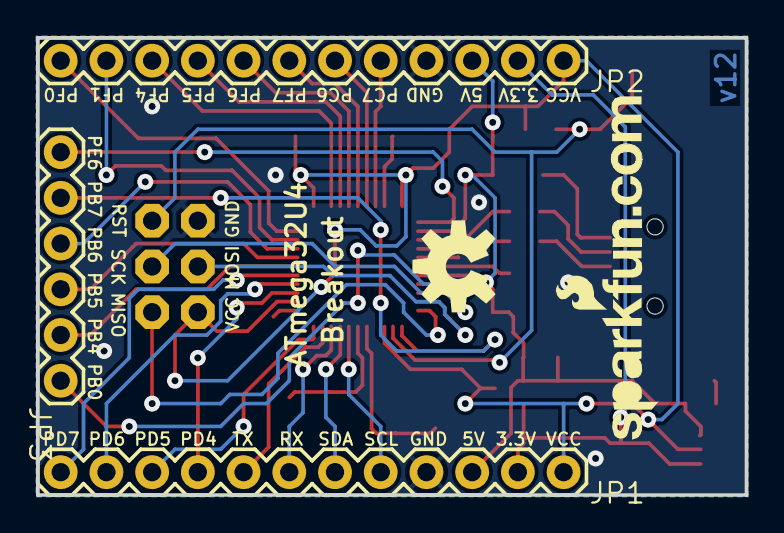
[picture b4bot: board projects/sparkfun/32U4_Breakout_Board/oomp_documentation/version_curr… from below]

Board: 2 copper layers, 39.4 x 25.4 mm, 30 parts (5 on the bottom side), 40 nets.

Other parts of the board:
JP5: LOGO-SFESK; SFE-LOGO-FLAME

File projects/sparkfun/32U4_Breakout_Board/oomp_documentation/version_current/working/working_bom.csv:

"Id";"Designator";"Footprint";"Quantity";"Designation";"Supplier and ref";
1;"JP7,JP6";"FIDUCIAL-1X2";2;"FIDUCIAL1X2";;;
2;"J1";"2X3";1;"AVR_SPI_PRG";;;
3;"C6,C9,C1,C7";"0603-CAP";4;"0.1uF";;;
4;"JP5";"SFE-LOGO-FLAME";1;"LOGO-SFESK";;;
5;"C8";"EIA3216";1;"10uF";;;
6;"R2,R3";"0603-RES";2;"22";;;
7;"C4,C5";"0603-CAP";2;"1uF";;;
8;"X1";"USB-MINIB";1;"USBSMD";;;
9;"R1";"0603-RES";1;"10k";;;
10;"R4";"0603-RES";1;"1k";;;
11;"C2,C3";"0603-CAP";2;"18pF";;;
12;"U2";"SOT23-5";1;"3.3V_REG_LDOSMD";;;
13;"U1";"QFN-44-NOPAD_1_1";1;"ATMEGA32U4";;;
14;"LED1";"LED-0603";1;"Power";;;
15;"S1";"TACTILE_SWITCH_SMD";1;"SWITCH-SMD";;;
16;"Y1";"CRYSTAL-SMD-5X3";1;"16MHz";;;
17;"SJ1";"SJ_3_PASTE2&3";1;"Power Select";;;
18;"F1";"PTC-1206";1;"PTCSMD";;;
19;"JP8";"SFE-NEW-WEBLOGO";1;"LOGO-SFENEW";;;
20;"JP3";"1X06";1;"";;;
21;"JP1,JP2";"1X12";2;"M12PTH";;;
22;"U$6";"OSHW-LOGO-M";1;"OSHW-LOGOM";;;

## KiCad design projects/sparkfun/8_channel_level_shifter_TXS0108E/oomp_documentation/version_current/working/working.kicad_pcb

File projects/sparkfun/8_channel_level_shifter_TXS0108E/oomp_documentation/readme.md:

# None

## Description
None/
## Schematic

## Bill of Materials
| Id | Designator | Footprint | Quantity | Designation | Supplier and ref |  |
| --- | --- | --- | --- | --- | --- | --- |
| 1 | U$12 | #A8#0 | 1 |  |  |  |
| 2 | C4,C3 | 0603 | 2 | 10uF |  |  |
| 3 | U$16 | #4#6 | 1 |  |  |  |
| 4 | U$18 | #B3#0 | 1 |  |  |  |
| 5 | R1 | 0603 | 1 | 100k |  |  |
| 6 | C2,C1 | 0603 | 2 | 0.1uF |  |  |
| 7 | U$21 | #OE#0 | 1 |  |  |  |
| 8 | U$33,U$47 | #0 | 2 |  |  |  |
| 9 | U$6 | #A2#0 | 1 |  |  |  |
| 10 | U$3,U$4 | #VA#0 | 2 |  |  |  |
| 11 | LOGO1,LOGO4 | OSHW-LOGO-S | 2 | OSHW-LOGOS |  |  |
| 12 | U$22,U$23 | #VB#0 | 2 |  |  |  |
| 13 | U$20 | #B1#0 | 1 |  |  |  |
| 14 | U$44,U$43 | TXS01080 | 2 |  |  |  |
| 15 | FD1,FD3,FD2,FD4 | FIDUCIAL-1X2 | 4 | FIDUCIAL1X2 |  |  |
| 16 | U$10 | #A6#0 | 1 |  |  |  |
| 17 | U$7 | #A3#0 | 1 |  |  |  |
| 18 | J1 | 1X11_NO_SILK | 1 |  |  |  |
| 19 | U1 | VFQFN-20 | 1 | TXS0108 |  |  |
| 20 | U$5 | #A1#0 | 1 |  |  |  |
| 21 | J2 | 1X10_NO_SILK | 1 |  |  |  |
| 22 | FRAME1 | CREATIVE_COMMONS | 1 | FRAME-LETTER |  |  |
| 23 | U$11 | #A7#0 | 1 |  |  |  |
| 24 | U$15 | #B6#0 | 1 |  |  |  |
| 25 | U$13 | #B8#0 | 1 |  |  |  |
| 26 | U$8 | #4#0 | 1 |  |  |  |
| 27 | U$46,U$48 | V0 | 2 |  |  |  |
| 28 | U$2,U$1,U$32,U$34 | #GND#0 | 4 |  |  |  |
| 29 | LOGO2,LOGO3 | SFE_LOGO_FLAME_.1 | 2 | SFE_LOGO_FLAME.1_INC<br>H |  |  |
| 30 | U$17 | #5#6 | 1 |  |  |  |
| 31 | U$9 | #5#0 | 1 |  |  |  |
| 32 | U$19 | #B2#0 | 1 |  |  |  |
| 33 | U$14 | #B7#0 | 1 |  |  |  |
| 34 | U$26 | #A3#3 | 1 |  |  |  |
| 35 | U$28 | #A5#5 | 1 |  |  |  |
| 36 | U$31 | #A8#9 | 1 |  |  |  |
| 37 | U$24 | #A1#2 | 1 |  |  |  |
| 38 | U$29 | #A6#6 | 1 |  |  |  |
| 39 | U$37 | #B6#9 | 1 |  |  |  |
| 40 | U$27 | #A4#4 | 1 |  |  |  |
| 41 | U$40 | #B3#9 | 1 |  |  |  |
| 42 | U$35 | #B8#9 | 1 |  |  |  |
| 43 | U$45 | #OE#1 | 1 |  |  |  |
| 44 | U$39 | #B4#9 | 1 |  |  |  |
| 45 | U$36 | #B7#9 | 1 |  |  |  |
| 46 | U$42 | #B1#9 | 1 |  |  |  |
| 47 | U$38 | #B5#9 | 1 |  |  |  |
| 48 | U$25 | #A2#2 | 1 |  |  |  |
| 49 | U$41 | #B2#9 | 1 |  |  |  |
| 50 | U$30 | #A7#8 | 1 |  |  |  |

## Images

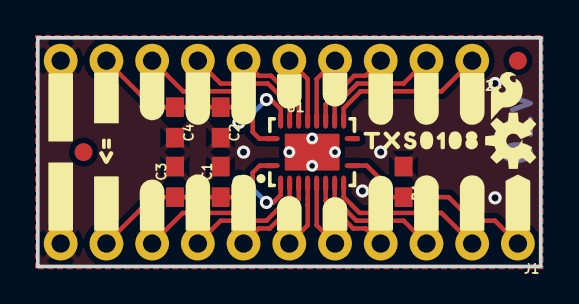
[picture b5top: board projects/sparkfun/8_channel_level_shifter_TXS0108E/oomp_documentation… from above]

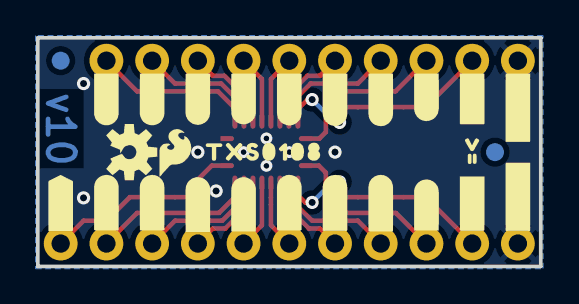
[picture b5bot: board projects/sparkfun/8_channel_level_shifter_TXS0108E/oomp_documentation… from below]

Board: 2 copper layers, 27.9 x 12.7 mm, 65 parts (28 on the bottom side), 20 nets.

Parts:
C1, C2: 0.1uF; 0603
C3, C4: 10uF; 0603
FD1, FD2, FD3, FD4: FIDUCIAL1X2; FIDUCIAL-1X2
FRAME1: FRAME-LETTER; CREATIVE_COMMONS
J1: 1X11_NO_SILK
J2: 1X10_NO_SILK
LOGO1, LOGO4: OSHW-LOGOS; OSHW-LOGO-S
LOGO2, LOGO3: SFE_LOGO_FLAME.1_INCH; SFE_LOGO_FLAME_.1
R1: 100k; 0603
U1: TXS0108; VFQFN-20
U$1, U$2, U$32, U$34: #GND#0
U$3, U$4: #VA#0
U$5: #A1#0
U$6: #A2#0
U$7: #A3#0
U$8: #4#0
U$9: #5#0
U$10: #A6#0
U$11: #A7#0
U$12: #A8#0
U$13: #B8#0
U$14: #B7#0
U$15: #B6#0
U$16: #4#6
U$17: #5#6
U$18: #B3#0
U$19: #B2#0
U$20: #B1#0
U$21: #OE#0
U$22, U$23: #VB#0
U$24: #A1#2
U$25: #A2#2
U$26: #A3#3
U$27: #A4#4
U$28: #A5#5
U$29: #A6#6
U$30: #A7#8
U$31: #A8#9
U$33, U$47: #0
U$35: #B8#9
U$36: #B7#9
U$37: #B6#9
U$38: #B5#9
U$39: #B4#9
U$40: #B3#9
U$41: #B2#9
U$42: #B1#9
U$43, U$44: TXS01080
U$45: #OE#1
U$46, U$48: V0

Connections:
A1: J1.9, U1.1
A2: J1.8, U1.3
A3: J1.7, U1.4
A4: J1.6, U1.5
A5: J1.5, U1.6
A6: J1.4, U1.7
A7: J1.3, U1.8
A8: J1.2, U1.9
B1: J2.8, U1.20
B2: J2.7, U1.18
B3: J2.6, U1.17
B4: J2.5, U1.16
B5: J2.4, U1.15
B6: J2.3, U1.14
B7: J2.2, U1.13
B8: J2.1, U1.12
GND: C1.2, C2.2, C3.2, C4.2, J1.11, J2.10, R1.1, U1.11, U1.EPAD
OE: J1.1, R1.2, U1.10
VCCA: C1.1, C3.1, J1.10, U1.2
VCCB: C2.1, C4.1, J2.9, U1.19

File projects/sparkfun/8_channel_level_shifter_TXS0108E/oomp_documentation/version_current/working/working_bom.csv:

"Id";"Designator";"Footprint";"Quantity";"Designation";"Supplier and ref";
1;"U$12";"#A8#0";1;"";;;
2;"C4,C3";"0603";2;"10uF";;;
3;"U$16";"#4#6";1;"";;;
4;"U$18";"#B3#0";1;"";;;
5;"R1";"0603";1;"100k";;;
6;"C2,C1";"0603";2;"0.1uF";;;
7;"U$21";"#OE#0";1;"";;;
8;"U$33,U$47";"#0";2;"";;;
9;"U$6";"#A2#0";1;"";;;
10;"U$3,U$4";"#VA#0";2;"";;;
11;"LOGO1,LOGO4";"OSHW-LOGO-S";2;"OSHW-LOGOS";;;
12;"U$22,U$23";"#VB#0";2;"";;;
13;"U$20";"#B1#0";1;"";;;
14;"U$44,U$43";"TXS01080";2;"";;;
15;"FD1,FD3,FD2,FD4";"FIDUCIAL-1X2";4;"FIDUCIAL1X2";;;
16;"U$10";"#A6#0";1;"";;;
17;"U$7";"#A3#0";1;"";;;
18;"J1";"1X11_NO_SILK";1;"";;;
19;"U1";"VFQFN-20";1;"TXS0108";;;
20;"U$5";"#A1#0";1;"";;;
21;"J2";"1X10_NO_SILK";1;"";;;
22;"FRAME1";"CREATIVE_COMMONS";1;"FRAME-LETTER";;;
23;"U$11";"#A7#0";1;"";;;
24;"U$15";"#B6#0";1;"";;;
25;"U$13";"#B8#0";1;"";;;
26;"U$8";"#4#0";1;"";;;
27;"U$46,U$48";"V0";2;"";;;
28;"U$2,U$1,U$32,U$34";"#GND#0";4;"";;;
29;"LOGO2,LOGO3";"SFE_LOGO_FLAME_.1";2;"SFE_LOGO_FLAME.1_INCH";;;
30;"U$17";"#5#6";1;"";;;
31;"U$9";"#5#0";1;"";;;
32;"U$19";"#B2#0";1;"";;;
33;"U$14";"#B7#0";1;"";;;
34;"U$26";"#A3#3";1;"";;;
35;"U$28";"#A5#5";1;"";;;
36;"U$31";"#A8#9";1;"";;;
37;"U$24";"#A1#2";1;"";;;
38;"U$29";"#A6#6";1;"";;;
39;"U$37";"#B6#9";1;"";;;
40;"U$27";"#A4#4";1;"";;;
41;"U$40";"#B3#9";1;"";;;
42;"U$35";"#B8#9";1;"";;;
43;"U$45";"#OE#1";1;"";;;
44;"U$39";"#B4#9";1;"";;;
45;"U$36";"#B7#9";1;"";;;
46;"U$42";"#B1#9";1;"";;;
47;"U$38";"#B5#9";1;"";;;
48;"U$25";"#A2#2";1;"";;;
49;"U$41";"#B2#9";1;"";;;
50;"U$30";"#A7#8";1;"";;;

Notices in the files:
projects/sparkfun/2D_Barcode_Scanner_Breakout/oomp_documentation/version_current/working/working.kicad_sch:
https://creativecommons.org/licenses/by-sa/4.0
Released under the Creative Commons
projects/sparkfun/32U4_Breakout_Board/oomp_documentation/version_current/working/working.kicad_sch:
http://creativecommons.org/licenses/by-sa/3.0
parts and their libraries:
Released under the Creative Commons Attribution Share-Alike 4.0 License
Released under the Creative Commons Attribution Share-Alike 3.0 License
